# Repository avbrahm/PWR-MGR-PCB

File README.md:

# PWR-MGR-PCB
Power Management PCB with USB-C.
Designed to handle single cell lipo charging with direct power path. Outputs regulated 3.3V for microcontrollers and ESD protected USB data lines.

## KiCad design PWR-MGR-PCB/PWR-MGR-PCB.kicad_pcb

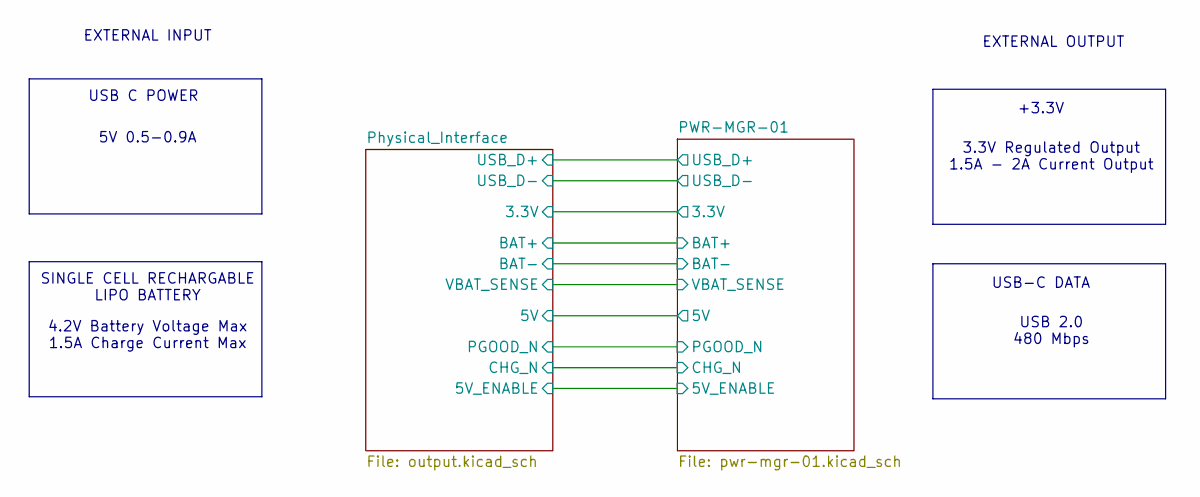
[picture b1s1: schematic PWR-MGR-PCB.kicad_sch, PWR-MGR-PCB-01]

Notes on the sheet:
SINGLE CELL RECHARGABLE LIPO BATTERY
USB 2.0 480 Mbps
3.3V Regulated Output 1.5A - 2A Current Output
5V 0.5-0.9A
EXTERNAL INPUT
4.2V Battery Voltage Max 1.5A Charge Current Max
USB-C DATA
EXTERNAL OUTPUT
USB C POWER
+3.3V

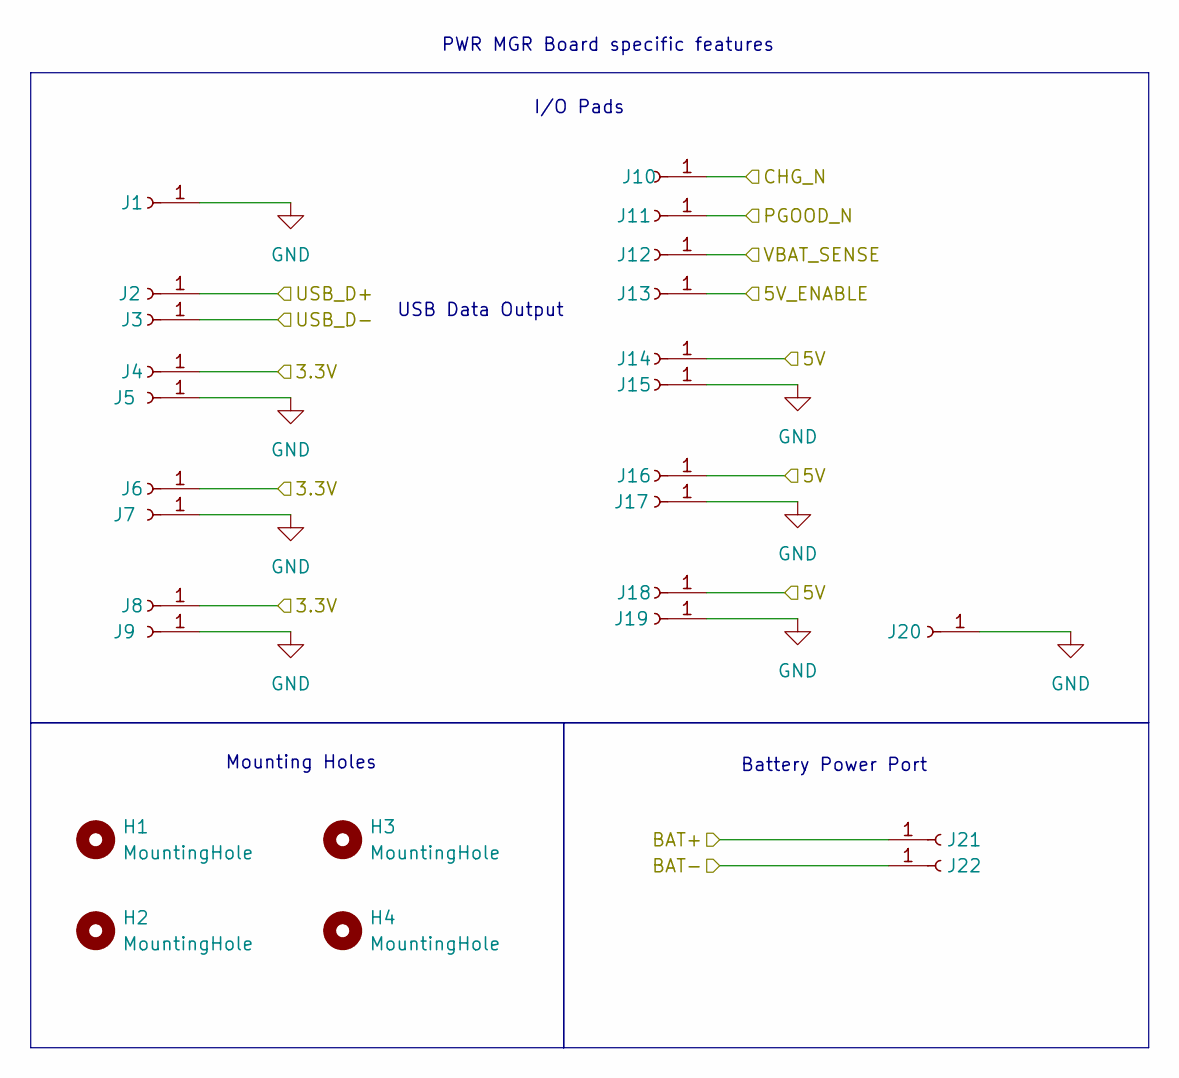
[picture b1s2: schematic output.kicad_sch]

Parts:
H1, H2, H3, H4: MountingHole; MountingHole_2.1mm
J1, J2, J3, J4, J5, J6, J7, J8, J9, J10, J11, J12, J13, J14, J15, J16, J17, J18, J19, J20, J21, J22: Conn_01x01_Socket; Drilled_Solder_Pad_0.6mm_3x1mm

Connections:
+3.3V: J4.1 (Pin_1_1), J6.1 (Pin_1_1), J8.1 (Pin_1_1); also elsewhere on the board
+5V: J14.1 (Pin_1_1), J16.1 (Pin_1_1), J18.1 (Pin_1_1); also elsewhere on the board
/PWR-MGR-01/5V_ENABLE: J13.1 (Pin_1_1); also elsewhere on the board
/PWR-MGR-01/BAT+: J21.1 (Pin_1_1); also elsewhere on the board
/PWR-MGR-01/CHG_N: J10.1 (Pin_1_1); also elsewhere on the board
/PWR-MGR-01/PGOOD_N: J11.1 (Pin_1_1); also elsewhere on the board
/PWR-MGR-01/USB_D+: J2.1 (Pin_1_1); also elsewhere on the board
/PWR-MGR-01/USB_D-: J3.1 (Pin_1_1); also elsewhere on the board
/PWR-MGR-01/VBAT_SENSE: J12.1 (Pin_1_1); also elsewhere on the board
GND: J1.1 (Pin_1_1), J5.1 (Pin_1_1), J7.1 (Pin_1_1), J9.1 (Pin_1_1), J15.1 (Pin_1_1), J17.1 (Pin_1_1), J19.1 (Pin_1_1), J20.1 (Pin_1_1), J22.1 (Pin_1_1); also elsewhere on the board

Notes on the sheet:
I/O Pads
Mounting Holes
Battery Power Port
PWR MGR Board specific features
USB Data Output

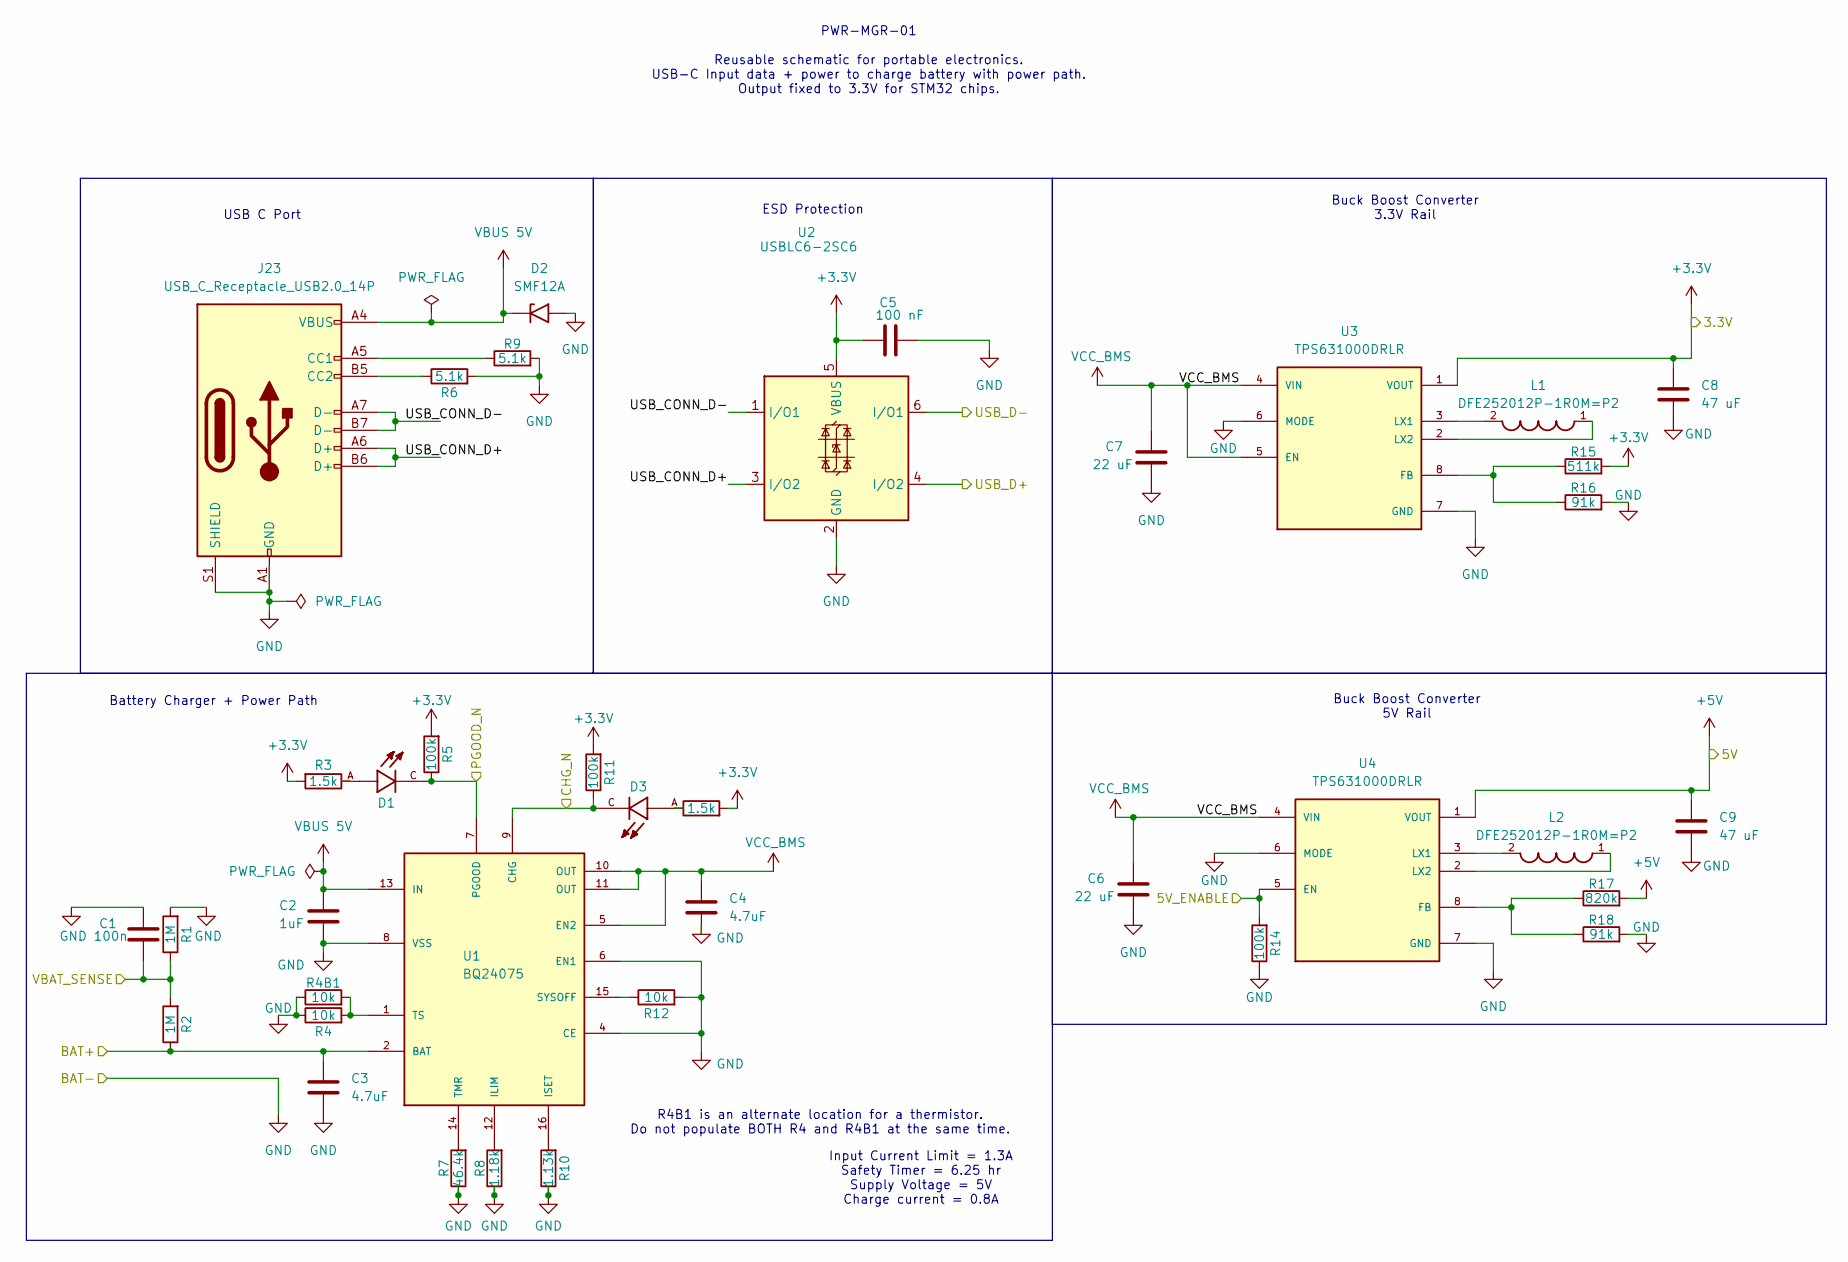
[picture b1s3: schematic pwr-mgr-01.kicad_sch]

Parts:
C1: 100n; C_0805_2012Metric; Manufacturer Part Number KAF21KR71H105JU
C2: 1uF; C_0805_2012Metric; Manufacturer Part Number KAF21KR71H105JU
C3, C4: 4.7uF; C_0805_2012Metric; Manufacturer Part Number CL21B475KBB6PNE
C5: 100 nF; C_0805_2012Metric; Manufacturer Part Number 08056D107MAT2A
C6, C7: 22 uF; C_0805_2012Metric; Manufacturer Part Number KAM21AT70J226MU
C8, C9: 47 uF; C_0805_2012Metric; Manufacturer Part Number CC0805MKX5R6BB476
D1, D3: SML-D12U1WT86; LED_SML-D12U1WT86; PARTREV 007
D2: SMF12A; D_SMF
J23: USB_C_Receptacle_USB2.0_14P; USB_C_Receptacle_GCT_USB4105-xx-A_16P_TopMnt_Horizontal; Manufacturer Part Number USB4105-GF-A
L1, L2: DFE252012P-1R0M=P2; INDC2520X120N
R1, R2: 1M; R_0805_2012Metric; Manufacturer Part Number MCU0805MD1002BP500
R3, R13: 1.5k; R_0805_2012Metric; Manufacturer Part Number RT73F2A1K5BTD
R4, R4B1: 10k; R_0805_2012Metric_Pad1.20x1.40mm_HandSolder; Manufacturer Part Number MCU0805MD1002BP500
R5, R11, R14: 100k; R_0805_2012Metric; Manufacturer Part Number MCU0805MD1002BP500
R6, R9: 5.1k; R_0805_2012Metric; Manufacturer Part Number ERA-6ARB512V
R7: 46.4k; R_0805_2012Metric; Manufacturer Part Number ERA-6AED4642V
R8: 1.18k; R_0805_2012Metric; Manufacturer Part Number ERJ-U06D1181V
R10: 1.13k; R_0805_2012Metric; Manufacturer Part Number PAT0805E1131BST1
R12: 10k; R_0805_2012Metric; Manufacturer Part Number MCU0805MD1002BP500
R15: 511k; R_0805_2012Metric; Manufacturer Part Number CR0805-FX-5113ELF
R16, R18: 91k; R_0805_2012Metric; Manufacturer Part Number ERA-6ARB913V
R17: 820k; R_0805_2012Metric; Manufacturer Part Number CR0805-FX-5113ELF
U1: BQ24075; QFN16; Manufacturer Part Number BQ24075RGTR
U2: USBLC6-2SC6; SOT-23-6; Manufacturer Part Number USBLC6-2SC6
U3, U4: TPS631000DRLR; SOT50P160X60-8N; PARTREV B

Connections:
+3.3V: C5.1, C8.1, R3.2, R5.2, R11.2, R13.2, R15.2, U2.5 (VBUS), U3.1 (VOUT); also elsewhere on the board
+5V: C9.1, R17.2, U4.1 (VOUT); also elsewhere on the board
/PWR-MGR-01/5V_ENABLE: R14.2, U4.5 (EN); also elsewhere on the board
/PWR-MGR-01/BAT+: C3.1, R2.1, U1.2 (BAT), U1.3 (BAT); also elsewhere on the board
/PWR-MGR-01/CHG_N: D3.C, R11.1, U1.9 (CHG); also elsewhere on the board
/PWR-MGR-01/PGOOD_N: D1.C, R5.1, U1.7 (PGOOD); also elsewhere on the board
/PWR-MGR-01/USB_CONN_D+: J23.A6 (D+), J23.B6 (D+), U2.3 (I/O2)
/PWR-MGR-01/USB_CONN_D-: J23.A7 (D-), J23.B7 (D-), U2.1 (I/O1)
/PWR-MGR-01/USB_D+: U2.4 (I/O2); also elsewhere on the board
/PWR-MGR-01/USB_D-: U2.6 (I/O1); also elsewhere on the board
/PWR-MGR-01/VBAT_SENSE: C1.2, R1.1, R2.2; also elsewhere on the board
GND: C1.1, C2.2, C3.2, C4.2, C5.2, C6.2, C7.2, C8.2, C9.2, D2.2 (A2), J23.A1 (GND), J23.A12 (GND), J23.B1 (GND), J23.B12 (GND), J23.S1 (SHIELD), R1.2, R4.1, R4B1.1, R6.2, R7.1, R8.1, R9.2, R10.1, R12.2, R14.1, R16.2, R18.2, U1.4 (CE), U1.6 (EN1), U1.8 (VSS), U1.TH (VSS), U2.2 (GND), U3.6 (MODE), U3.7 (GND), U4.6 (MODE), U4.7 (GND); also elsewhere on the board
unnamed: D1.A, R3.1
unnamed: D3.A, R13.1
unnamed: J23.A5 (CC1), R9.1
unnamed: J23.B5 (CC2), R6.1
unnamed: R8.2, U1.12 (ILIM)
unnamed: R10.2, U1.16 (ISET)
unnamed: R12.1, U1.15 (SYSOFF)
unnamed: R7.2, U1.14 (TMR)
unnamed: R4.2, R4B1.2, U1.1 (TS)
unnamed: R15.1, R16.1, U3.8 (FB)
unnamed: L1.2, U3.3 (LX1)
unnamed: L1.1, U3.2 (LX2)
unnamed: R17.1, R18.1, U4.8 (FB)
unnamed: L2.2, U4.3 (LX1)
unnamed: L2.1, U4.2 (LX2)
VBUS 5V: C2.1, D2.1 (A1), J23.A4 (VBUS), J23.A9 (VBUS), J23.B4 (VBUS), J23.B9 (VBUS), U1.13 (IN)
VCC_BMS: C4.1, C6.1, C7.1, U1.5 (EN2), U1.10 (OUT), U1.11 (OUT), U3.4 (VIN), U3.5 (EN), U4.4 (VIN)

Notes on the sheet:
Input Current Limit = 1.3A Safety Timer = 6.25 hr Supply Voltage = 5V Charge current = 0.8A
Battery Charger + Power Path
Buck Boost Converter 3.3V Rail
R4B1 is an alternate location for a thermistor. Do not populate BOTH R4 and R4B1 at the same time.
Buck Boost Converter 5V Rail
USB C Port
ESD Protection
PWR-MGR-01 Reusable schematic for portable electronics. USB-C Input data + power to charge battery with power path. Output fixed to 3.3V for STM32 chips.

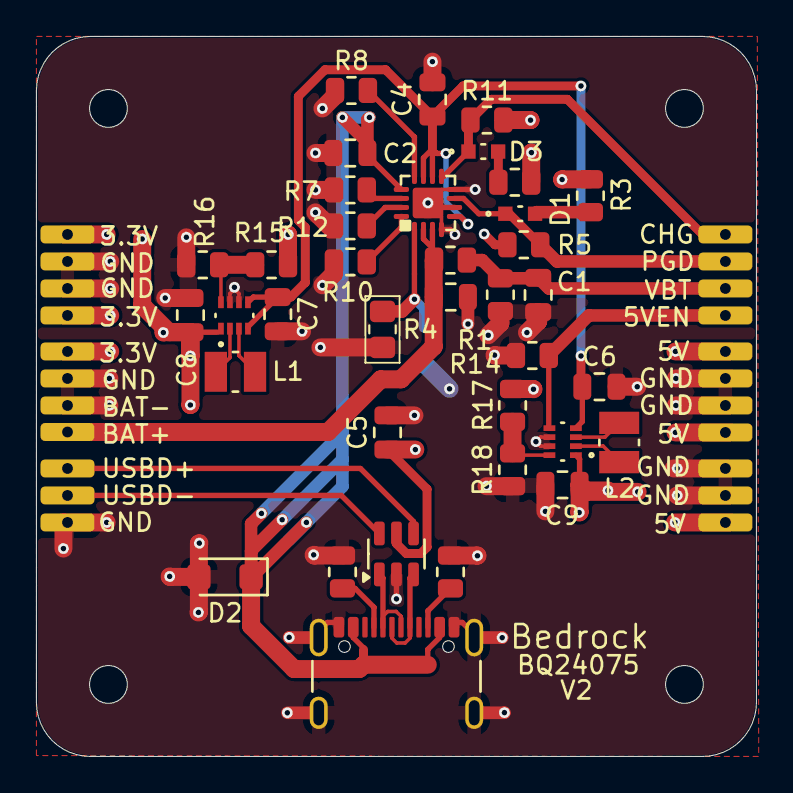
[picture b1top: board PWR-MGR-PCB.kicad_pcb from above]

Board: 4 copper layers, 40.0 x 40.0 mm, 64 parts (1 on the bottom side), 29 nets.

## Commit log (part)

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2025-09-09 Init Repo
2025-09-10 Add test ports
2025-09-10 Start layout
2025-09-14 Layout PCB
2025-09-14 Resize board
2025-09-14 Fix board layout
2025-09-18 Layout board
2025-09-19 Route board
2025-09-24 Reroute board
2025-09-30 Sync latest fixes
2025-09-30 Update diode component
2025-10-07 Begin placing board
2025-10-07 Refine outline
2025-10-07 Start placement
2025-10-14 Start bq2407 zones
2025-10-16 Fix Z-tilt
2025-10-16 Add filled zones around battery charger
2025-10-16 Add power LEDs, connect battery terminal
2025-10-18 Replace LDO with buck boost converter
2025-10-18 Add inductor
2025-10-18 Configure buck boost converter
2025-10-22 Route buck boost converter, add ground plane
2025-10-22 Add USB lines, add mount holes, add power port
2025-10-24 Format sheet for reusability
2025-10-24 Stop tracking backups
2025-10-24 Remove windows file extension from gitignore
2025-10-24 Fix naming
2025-10-28 Add image
2025-11-09 Change USB-C to 6 pin
2025-11-13 Switch back to 16 pin
2025-11-14 Begin layout
2025-11-19 New layout
2025-11-20 Complete USB-C tracing
2025-11-26 Improve USB routing
2025-11-26 Finish USB data routing, connect VBUS to BQ2407
2025-11-27 Optimize trace width for current
2025-11-27 Connect VBATT
2025-11-28 Layout buck boost converter
2025-12-02 Change zone connection types, change connectors, add zones for buck boost converter
2025-12-02 Routing complete
2025-12-04 DRC checks
2025-12-05 Solve DRC
2025-12-07 Add BQ24075
2025-12-10 Route BQ24075
2025-12-10 Fix SBU tracks
2025-12-16 Solve all DRC issues
2025-12-16 Solve all ERC issues
2025-12-18 Add MPNs and generate DRL file
2025-12-27 Adjust boost converter FB pin
2025-12-28 Pull down SYSOFF
2026-01-07 Shorten traces
2026-01-07 Improve capacitor position
2026-01-11 Update layout, optimize sub-sheet for reusability
2026-01-11 Fill in top plane, remove outdated files
2026-01-15 Update fabrication outputs
2026-01-16 Production ready!
2026-01-20 Update imaeg
2026-03-24 Update gitignore
2026-06-16 align ports
